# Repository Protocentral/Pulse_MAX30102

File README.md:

Pulse
================================

[Don't have it yet? Buy one here: Pulse+ Pulse-Ox & Heart Rate Sensor based on MAX30102 (PC-MED-0402)](https://protocentral.com/product/pulse-3-pulse-ox-heart-rate-sensor-based-on-max30102-qwiic-compatible/)

This is the new Pulse Plus building on our earlier Pulse board by adding the new MAX30102 chip from Maxim that provides better performance.

The Pulse sensor board from ProtoCentral is our new addition to our open medical hardware line-up. Maxim's MAX30100 is a great new product that combines everything required for a pulse oximeter (including the LEDs and Photodiode !!) on a single tiny chip.

Measuring 14 mm wide and 40 mm long, this board is easily wearable on the finger to measure the pulse of blood. We even provide a Velcro strap to hold it.
Important Note: This device is only meant to be used for Research purposes and is NOT to be used as a medical device. This product is not FDA, CE or FCC approved for consumer use. 

Features:
* Integrates a complete pulse oximeter including the optics. No need for a separate probe. 
* Easy-to-use I2C interface to connect to any host microcontroller
* 880 nm Infrared and 660 nm Red LEDs
* Arduino library available
* Calculates Spo2 values with provided code
* Real-time display of PPG (Photoplethysmogram)

Includes:
----------
* 1x ProtoCentral Pulse Oximeter breakout
* 1x Welgro strap

Repository Contents
-------------------
* **/Software** - Arduino and Processing library and example sketches.
* **/Hardware** - All Eagle design files (.brd, .sch)
* **/extras** -   includes the datasheet

Wiring the Breakout to your Arduino
------------------------------------
Connection with the Arduino board is as follows:
 
|Pulse pin label   | Arduino Connection   |Pin Function      |
|----------------- |:--------------------:|-----------------:|
| VCC              | +5V                  |  Supply voltage  |             
| SCL              | A5                   |  Serial clock    |
| SDA              | A4                   |  Serial data     |
| GND              |                      |  Gnd             |

Using Processing - Data Visualization Software (New!)
-----------------------------------------------------
 Processing is a data visualization software, in existence since 2001, used by artists and scientists alike. It’s an open source coding framework based on Java. If you are familiar with the Arduino environment, the Processing IDE is similar and you won’t have much of a learning curve to climb!
 
 The following are the steps to run the code:

### 1. Download Processing for your operating system

 Download the processing ide latest version from the link

* [MAC] (http://download.processing.org/processing-3.2.1-macosx.zip)
* [Linux 32-bit] (http://download.processing.org/processing-3.2.1-linux32.tgz)
* [Linux 64-bit] (http://download.processing.org/processing-3.2.1-linux64.tgz)
* [Windows 32-bit] (http://download.processing.org/processing-3.2.1-windows32.zip)
* [Windows 64-bit] (http://download.processing.org/processing-3.2.1-windows64.zip)

 Once downloaded, unzip the archive and install the app as per your OS.

### 2. Download the Processing code for Pulse Oximeter visualization

 a. Download the necessary files & directories or clone to your desktop from GitHub.

 b. Unzipping the archive should make a folder by name Pulse that contains the visualization code.

 c. Locate the Processing sketchbook directory on your computer. This should have been created automatically when you installed processing. Depending on your operating system, the path will be as follows:

* On Windows: c:/My Documents/Processing/
* On MAC: /Users/your_user_name/Documents/Processing/
* On Linux: /Home/your_user_name/sketchbook/

**Note:** This directory appears as "Processing" on Windows/Mac, and goes by the name "Sketchbook" on Linux. Create a subdirectory by name "libraries" if one doesn't exist already.

 d. From the above mentioned "Pulse" directory Copy/Move the contents of the Pulse-master/Software/Processing/openview_oximeter folder to the Processing sketchbook directory which is also mentioned above (Locate the Processing sketchbook)

 e. Finally, copy the G4P directories from Pulse-master\Processing\libraries and paste them into the libraries directory of your Processing sketchbook.

 f. You are all set now to get your first PPG wave form and SpO2 reading visualized from the Pulse!

### 3. Open Processing & launch the openview_oximeter

 a. If Processing IDE was open, close it and reopen to refresh the libraries and sketches. The repositories are not refreshed if the IDE was open while the Sketches and Libraries were being updated.

 b. Double-click any of the .pde files in the openview_oximeter directory to open all of the pulse oximeter code in the Processing IDE.

 c. If everything done so far was good, clicking the "run" button on the top left corner of the IDE, should run the code! If it does not, make sure you installed your libraries correctly.

 d. Once the GUI is running, select the port connect with pulse oximeter shield from the "SELECT PORT" dropdown as shown in the figure below

 e. Once the port selection is appropriate the START button gets enabled. Click "START" to initiate visualization

 f. You should see the PPG ( RED and IR) waves generated with the values obtained from the Pulse as shown below.

License Information
===================

This product is open source! Both, our hardware and software are open source and licensed under the following licenses:

Hardware
---------

**All hardware is released under [Creative Commons Share-alike 4.0 International](http://creativecommons.org/licenses/by-sa/4.0/).**

You are free to:

* Share — copy and redistribute the material in any medium or format
* Adapt — remix, transform, and build upon the material for any purpose, even commercially.
The licensor cannot revoke these freedoms as long as you follow the license terms.

Under the following terms:

* Attribution — You must give appropriate credit, provide a link to the license, and indicate if changes were made. You may do so in any reasonable manner, but not in any way that suggests the licensor endorses you or your use.
* ShareAlike — If you remix, transform, or build upon the material, you must distribute your contributions under the same license as the original.

Software
--------

**All software is released under the MIT License(http://opensource.org/licenses/MIT).**

THE SOFTWARE IS PROVIDED "AS IS", WITHOUT WARRANTY OF ANY KIND, EXPRESS OR IMPLIED, INCLUDING BUT NOT LIMITED TO THE WARRANTIES OF MERCHANTABILITY, FITNESS FOR A PARTICULAR PURPOSE AND NONINFRINGEMENT. IN NO EVENT SHALL THE AUTHORS OR COPYRIGHT HOLDERS BE LIABLE FOR ANY CLAIM, DAMAGES OR OTHER LIABILITY, WHETHER IN AN ACTION OF CONTRACT, TORT OR OTHERWISE, ARISING FROM, OUT OF OR IN CONNECTION WITH THE SOFTWARE OR THE USE OR OTHER DEALINGS IN THE SOFTWARE.

Please check [*LICENSE.md*](LICENSE.md) for detailed license descriptions.

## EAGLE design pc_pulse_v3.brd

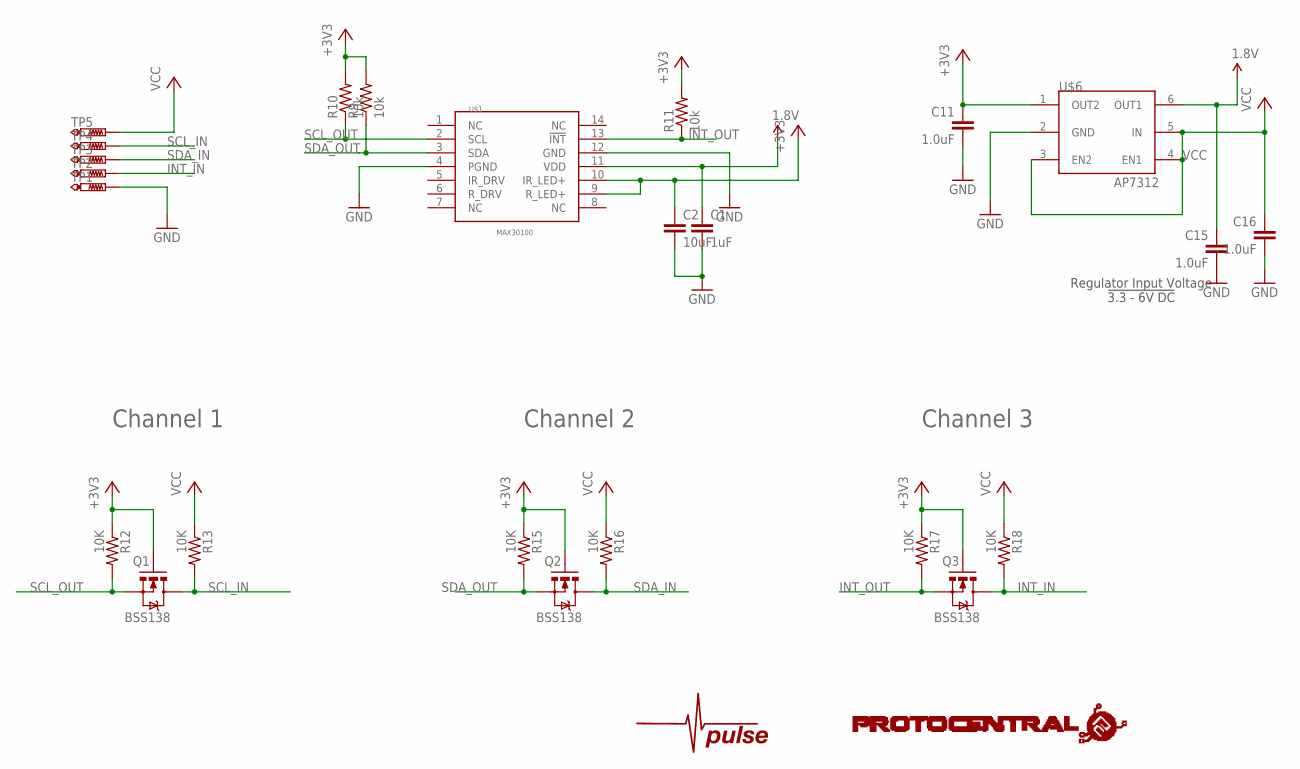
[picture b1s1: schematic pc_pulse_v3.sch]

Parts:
C1: 1uF; C0805
C2: 10uF; C0805
C11, C15, C16: 1.0uF; 0805
Q1, Q2, Q3: BSS138; SOT23-3
R9, R10, R11: 10k; R0402
R12, R13, R15, R16, R17, R18: 10K; 0402-RES
TP1, TP2, TP3, TP4, TP5: PTR1TP20SQ; TP20SQ
U$1: MAX30100; OESIP-14
U$3: PROTY-LOGO; LOGO-PROTY
U$4: PULSE
U$6: AP7312; SOT26
U$7: PROTY_LOGO_WITH_TEXT; PROTY_WITH_TEXT

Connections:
1.8V: C1.1, C15.1, U$1.11 (VDD), U$6.6 (OUT1)
+3V3: C2.1, C11.1, Q1.1 (G), Q2.1 (G), Q3.1 (G), R9.2, R10.2, R11.2, R12.1, R15.1, R17.1, U$1.9 (R_LED+), U$1.10 (IR_LED+), U$6.1 (OUT2)
GND: C1.2, C2.2, C11.2, C15.2, C16.2, TP1.TP, U$1.4 (PGND), U$1.12 (GND), U$6.2 (GND)
INT_IN: Q3.3 (D), R18.2, TP2.TP
INT_OUT: Q3.2 (S), R11.1, R17.2, U$1.13 (!INT)
SCL_IN: Q1.3 (D), R13.2, TP4.TP
SCL_OUT: Q1.2 (S), R10.1, R12.2, U$1.2 (SCL)
SDA_IN: Q2.3 (D), R16.2, TP3.TP
SDA_OUT: Q2.2 (S), R9.1, R15.2, U$1.3 (SDA)
VCC: C16.1, R13.1, R16.1, R18.1, TP5.TP, U$6.3 (EN2), U$6.4 (EN1), U$6.5 (IN)

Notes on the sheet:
Channel 1
Channel 2
Channel 3
Regulator Input Voltage !3.3 - 6V DC!

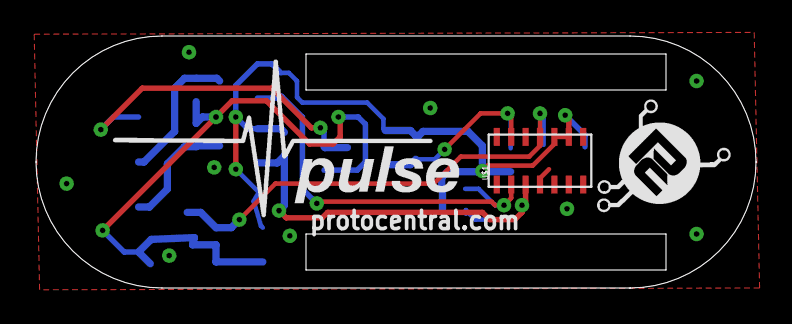
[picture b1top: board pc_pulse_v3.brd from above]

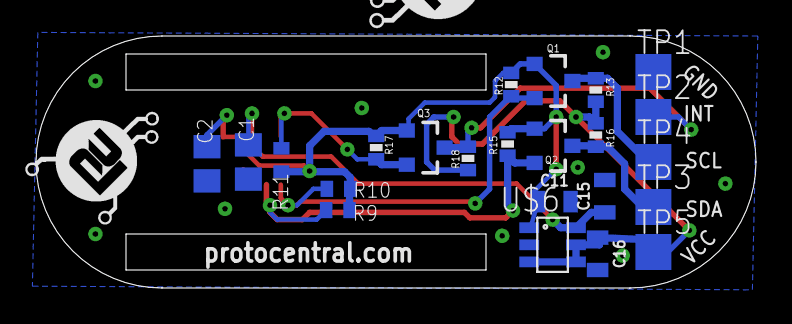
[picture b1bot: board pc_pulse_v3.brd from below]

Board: 4 copper layers, 40.0 x 14.0 mm, 28 parts (25 on the bottom side), 10 nets.

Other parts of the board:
U$5: PROTY-LOGO; LOGO-PROTY

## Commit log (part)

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2017-01-12 :octocat: Added .gitattributes & .gitignore files
2017-01-16 upadated sketch
2017-01-16 updated sketch
2017-04-19 fixed data saturatiion
2018-05-16 Create Hardware
2018-05-16 Create pc_pulse_v3

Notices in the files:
README.md:
CC-BY-SA-4.0
parts and their libraries:
SparkFun-Aesthetics: Licensing: Creative Commons ShareAlike 4.0 International - https://creativecommons.org/licenses/by-sa/4.0
